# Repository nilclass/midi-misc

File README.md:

# misc midi hardware stuff

A place to put my MIDI related schematics & code.

Nothing special or new here, just a reference for myself.

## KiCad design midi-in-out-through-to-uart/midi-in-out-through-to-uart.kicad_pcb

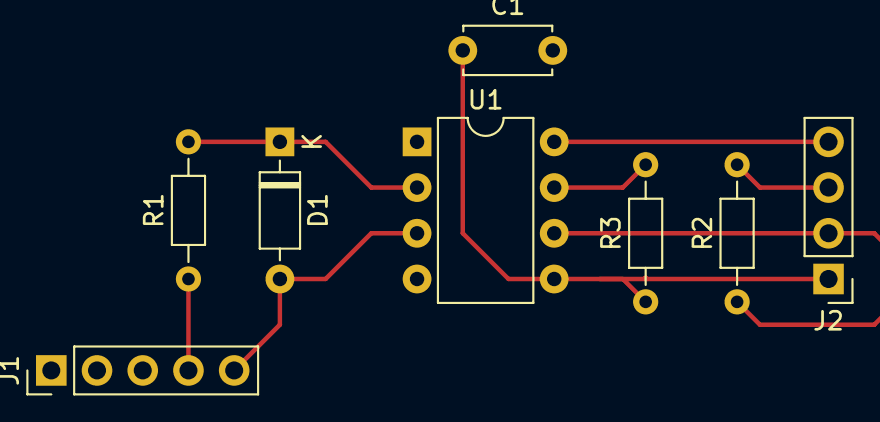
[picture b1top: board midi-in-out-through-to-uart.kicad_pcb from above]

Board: 2 copper layers, 8 parts (0 on the bottom side), 8 nets.

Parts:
C1: 100n; C_Disc_D4.7mm_W2.5mm_P5.00mm
D1: 1N4148; D_DO-35_SOD27_P7.62mm_Horizontal
J1: DIN-5_180degree; PinHeader_1x05_P2.54mm_Vertical
J2: Conn_01x04_Pin; PinHeader_1x04_P2.54mm_Vertical
R1: 220; R_Axial_DIN0204_L3.6mm_D1.6mm_P7.62mm_Horizontal
R2: 1k; R_Axial_DIN0204_L3.6mm_D1.6mm_P7.62mm_Horizontal
R3: 10k; R_Axial_DIN0204_L3.6mm_D1.6mm_P7.62mm_Horizontal
U1: 6N138; DIP-8_W7.62mm

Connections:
+5V: C1.2, J2.4, U1.8 (VCC)
GND: C1.1, J2.1, R3.1, U1.5 (GND)
unnamed: D1.2 (A), J1.5, U1.3 (C2)
unnamed: D1.1 (K), R1.2, U1.2 (C1)
unnamed: J1.4, R1.1
unnamed: R3.2, U1.7 (VO1)
UART RX: J2.2, R2.1, U1.6 (VO2)
VCC: J2.3, R2.2

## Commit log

2023-07-16 init
2023-07-16 add schematics for IN+OUT+THROUGH boards
2023-07-16 add midi-gateway code
